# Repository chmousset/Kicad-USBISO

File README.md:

# USB Isolator

The title says it all: it isolates an USB port.

It will be useful to break ground loops, or to protect your laptop when working on high voltage devices such as an AC motor controller.
Commercially-available offerings either lacked proper isolation for working with mains voltage (only 1kV isolation rating), full USB 2.0 speed (limited to 12Mbps), partial USB3.0 support, or a high price point (onwards to 1000€ range).

The ADUM1366 is the main chip that isolates USB2.0 LS, FS and HS (1.5, 12 and 480Mbps respectively). It's tested at 3750V for 1 minute.
5V @1A of output power is provided through the onboard REC5A DC/DC converter, which is tested at 2kV for 1 min. If higher insulation is required, other DC/DC converters with similar package and 3 kV or more rating exist.

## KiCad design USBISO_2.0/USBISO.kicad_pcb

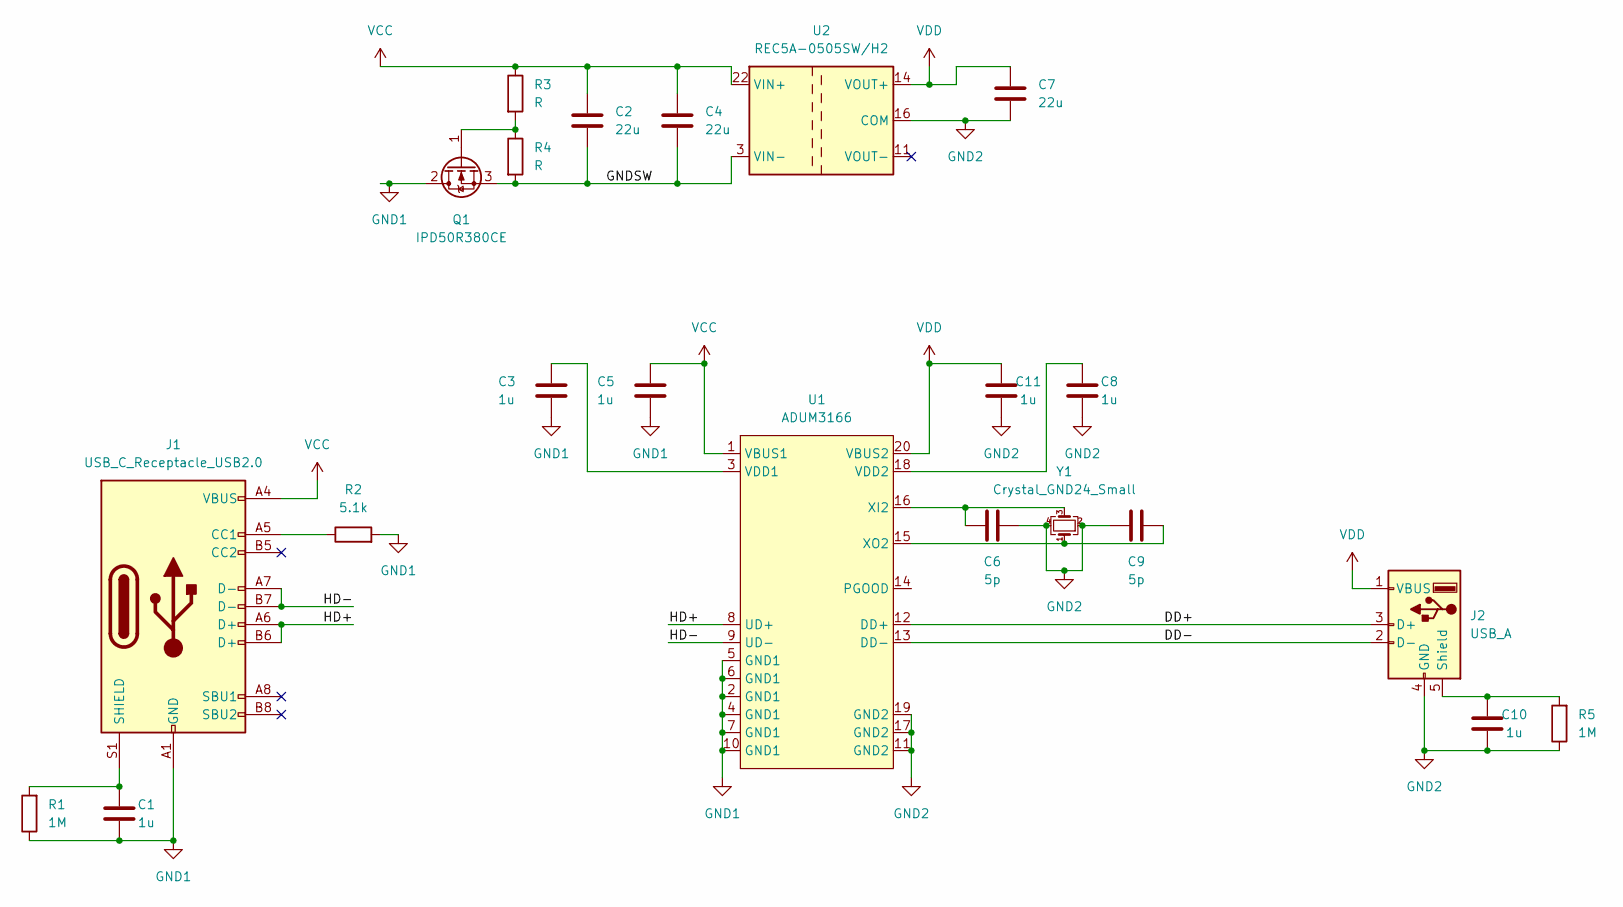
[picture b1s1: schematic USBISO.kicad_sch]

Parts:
C1, C3, C5, C8, C10, C11: 1u; C_0805_2012Metric
C2, C4, C7: 22u; C_1210_3225Metric
C6, C9: 5p; C_0603_1608Metric
J1: USB_C_Receptacle_USB2.0; USB_C_Receptacle_GCT_USB4085
J2: USB_A; USB_A_CONNFLY_DS1095-WNR0
Q1: IPD50R380CE; TO-252-2
R1, R5: 1M; R_0603_1608Metric
R2: 5.1k; R_0603_1608Metric
R3, R4: R; R_0603_1608Metric
U1: ADUM3166; SSOP-20_5.3x7.2mm_P0.65mm
U2: REC5A-0505SW/H2; Converter_DCDC_XP_POWER_JTExxxxDxx_THT
Y1: Crystal_GND24_Small; Crystal_SMD_3225-4Pin_3.2x2.5mm

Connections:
/DD+: J2.3 (D+), U1.12 (DD+)
/DD-: J2.2 (D-), U1.13 (DD-)
/GNDSW: C2.2, C4.2, Q1.3 (S), R4.2, U2.2 (VIN-), U2.3 (VIN-)
/HD+: J1.A6 (D+), J1.B6 (D+), U1.8 (UD+)
/HD-: J1.A7 (D-), J1.B7 (D-), U1.9 (UD-)
GND1: C1.1, C3.2, C5.2, J1.A1 (GND), J1.A12 (GND), J1.B1 (GND), J1.B12 (GND), Q1.2 (D), R1.1, R2.2, U1.2 (GND1), U1.4 (GND1), U1.5 (GND1), U1.6 (GND1), U1.7 (GND1), U1.10 (GND1)
GND2: C6.2, C7.2, C8.1, C9.1, C10.1, C11.1, J2.4 (GND), R5.1, U1.11 (GND2), U1.17 (GND2), U1.19 (GND2), U2.9 (COM), U2.16 (COM), Y1.2, Y1.4
unnamed: C1.2, J1.S1 (SHIELD), R1.2
unnamed: C3.1, U1.3 (VDD1)
unnamed: C6.1, U1.16 (XI2), Y1.3
unnamed: C8.2, U1.18 (VDD2)
unnamed: C9.2, U1.15 (XO2), Y1.1
unnamed: C10.2, J2.5 (Shield), R5.2
unnamed: J1.A5 (CC1), R2.1
unnamed: Q1.1 (G), R3.2, R4.1
VCC: C2.1, C4.1, C5.1, J1.A4 (VBUS), J1.A9 (VBUS), J1.B4 (VBUS), J1.B9 (VBUS), R3.1, U1.1 (VBUS1), U2.22 (VIN+), U2.23 (VIN+)
VDD: C7.1, C11.2, J2.1 (VBUS), U1.20 (VBUS2), U2.14 (VOUT+)

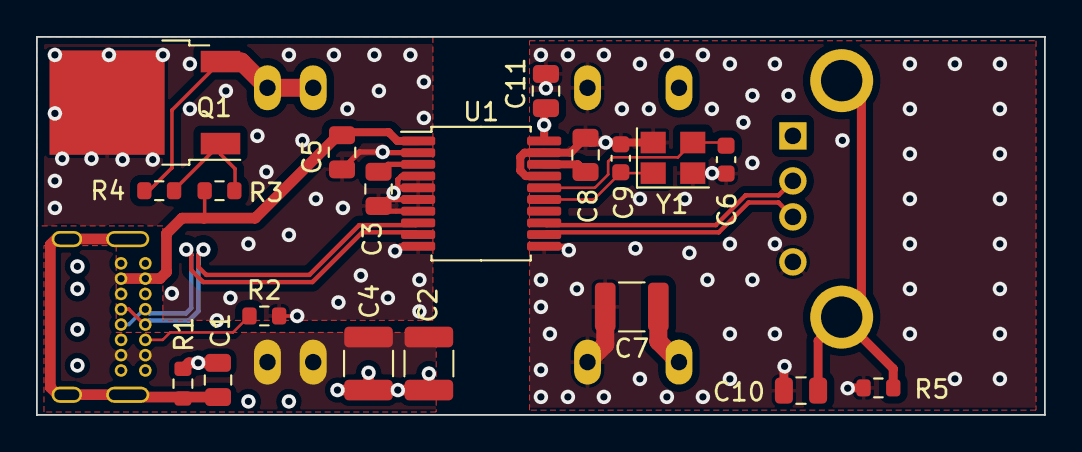
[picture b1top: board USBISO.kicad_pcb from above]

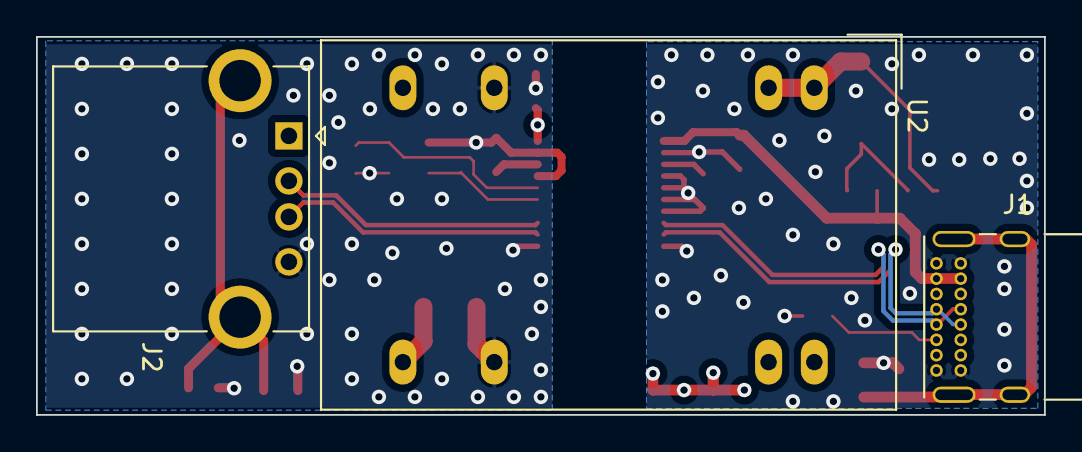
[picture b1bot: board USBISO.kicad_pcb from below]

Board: 4 copper layers, 56.0 x 21.0 mm, 22 parts (3 on the bottom side), 17 nets.

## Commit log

2024-04-13 [init] as produced and validated
